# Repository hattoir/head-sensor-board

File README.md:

# 🧠 Serpens Head Sensor Board

> Prototype head sensor PCB for the Serpens snake-shaped pet robot.

Serpensの頭部に搭載するために設計している、
**試作用センサ基板**です。

XIAO ESP32S3 Senseを中心に、

- VL53L1X ToFセンサ ×2
- NSSW157T 白色LED ×2
- MOSFET PWM駆動
- I2C
- Test Points
- 外付けLEDヘッダ

をまとめています。

主な目的は、

- 床端・崖の検出
- 頭部周辺の距離センシング
- LEDによる表現・照明試験

です。

> ⚠️ 現在は設計・製造データ生成まで完了していますが、
> 実基板はまだ発注・製造していません。

---

## 📊 Current Status

| Area | Status |
|---|---|
| Specification | ✅ Complete |
| Schematic | ✅ ERC 0 |
| PCB Layout | ✅ Complete |
| Routing | ✅ Complete |
| DRC | ✅ 0 violations |
| 3D Render | ✅ Complete |
| Gerber / Drill | ✅ Generated |
| BOM | ✅ Generated |
| Manufacturing | ⚪ Not ordered |
| Hardware Verification | ⚪ Not tested |

---

## 🖼 PCB Preview

<!-- ここに今ある3Dレンダリング画像 -->

### Top / Angle View

> ※ 実物写真ではなく、KiCad上の3Dレンダリングです。

---

## ⚙️ Main Components

- XIAO ESP32S3 Sense
- VL53L1X ×2
- NSSW157T ×2
- AO3400A / MOSFET
- I2C pull-up
- Test points

---

## 📐 Board

- Size: **44 × 28 mm**
- Layers: **2**
- M2 mounting holes ×2
- GND plane on both layers
- USB-C access from board edge
- ToF headers on long edges
- LED / external LED headers on right side

---

## 🔬 Verification

現在までに、

- ERC: 0 errors
- DRC: 0 violations
- Unconnected: 0
- Schematic / PCB mismatch: 0
- Silkscreen clearance check
- Gerber verification

を行っています。

ただし、
実機に接続しての電源・ToF・LED動作確認は未実施です。

---

> ## ⚠ 電源の運用上の注意（User 指示 2026-10-01。回路図の注記 H にも同じ内容）
> 1. **5V は試験用の選択肢で、既定は 3V3。** 5V にしたときの合計 **493 mA は USB 2.0 の 500 mA ぎりぎり**（余裕 7 mA）。XIAO の 5V ピンの電流能力は未確認。
> 2. **3V3 は、Wi-Fi 送信・撮影・LED 100 %・ToF ピークを同時にしない運用が必要。** **実機で XIAO の 5V 入力電流を測るまで。**（Seeed の条件不明の 0.65 A を上限と見ると 3V3 の合計は 808 mA = Seeed の「700 mA」の 115 %。[docs/spec.md](docs/spec.md) §4.3）

## 進み具合

| Stage | 内容 | 状態 |
|---|---|---|
| 1 | 仕様と部品表 | 完了（2026-10-01、承認済み） |
| 2 | 回路図と ERC（エラー 0） | 完了（2026-10-01、User 確認済み。ERC 0 件） |
| 3 | 外形と部品配置案（配線なし） | 完了（2026-10-01、User 確認済み） |
| 4 | 外形 44×28 mm、配線、DRC（違反 0・未接続 0・回路図との不一致 0）、3D ビュー、製造データ | **完了（2026-10-02）。製造データ（ガーバー・ドリル・位置ファイル・BOM、ZIP）は [gerbers/](gerbers/) に出した。User の最終確認待ちで、発注はしていない**（[docs/spec.md](docs/spec.md) §6・§7） |

## 配線後の配置（Stage 4）

- **44 × 28 mm、角 R1、M2 穴 ×2**（右の 2 つの角、縁から 2.1 mm）。2 層。`python tools/make_board.py --width W --height H` で、外形・配置・配線・DRC まで作り直せる（[再生成と検証](#再生成と検証)）。
- **USB-C は左の縁**（左下に矢印と「USB-C」の刻印）、**LED（D1/D2）と外付け LED ヘッダ（J3/J4）は右寄りの縁**、**ToF ヘッダ（J1/J2）は上下の長辺の縁**（6 本の信号名を刻印）、TP は上面。**「L」「R」の刻印**あり。
- **下半分 = L チャンネル、上半分 = R チャンネル**（上面から見て USB-C を左にしたとき）。基板上の L/R はロボットの左右とは限らない（ジャンパー線で左右は自由に決められる）。
- 配線: **電源（+3V3・+5V）0.5 mm、LED の電流の経路 0.4 mm、信号 0.25 mm**。GND は両面のベタ。ビア 28 個。I2C の長さは SDA 32 mm・SCL 38 mm。
- **DRC: 違反 0 件**（クリアランス 0.2 mm・縁 0.5 mm・未接続 0・回路図との不一致 0。プロジェクトで「無視」にしていた 4 種の検査も有効にして 0 件）。[docs/drc_report.txt](docs/drc_report.txt)
- **刻印の検査**（`tools/check_board.py`）: 上面の刻印 137 個が、ランド・ほかの刻印と **0.15 mm 以上**、ヘッダの樹脂部（2.54 mm 角）と 0.05 mm 以上、XIAO の外形・基板の縁と離れている。**シルクの線は全部 0.15 mm 以上、文字の高さは 0.8 mm**（2026-10-05 に 0.12 → 0.15 mm に直した。発注先 4 社の公開仕様との照合 → [docs/fab_check.md](docs/fab_check.md)。**JLCPCB の標準の文字（高さ 1.0 mm 以上）だけは未達で、注文画面の「高精度の文字」を選べば通る**。PCBWay・Elecrow・Seeed Fusion は通る）。J1/J2 の信号名は樹脂部の外に 2 段で置き、奥の段には樹脂部の手前までの引き出し線を引いた。
- XIAO の下（ソケットの内側）に小さい部品を置き、裏面は GND ベタ。Sense 拡張ボード（カメラ・microSD）は XIAO の上面に載り、基板側の部品とは干渉しない（出っ張りは未確認。[docs/spec.md](docs/spec.md) §6.5）。

| | |
|---|---|
|  |  |
| 斜め上から（XIAO・拡張ボードは**簡易な箱**。高さは仮） | 真上から（XIAO を外した状態） |

そのほか: [層ごとの配線](docs/routing_layers.png)（表面 F.Cu・裏面 B.Cu）、[3D 真上](docs/board_3d_top.png)、[3D 裏面](docs/board_3d_bottom.png)。

## ToF 小基板のピン配置と、ジャンパー線の対応表（**現物が届いたら埋める**）

J1 / J2 の 6 本は、ToF 小基板（VL53L1X、Amazon B083Z316NC）へジャンパー線でつなぐ。**小基板のピン配置は販売ページに記載がなく、未確認。** ヘッダの並び（上面に信号名を刻印）は仮で、**小基板の並びが違っても基板の作り直しは要らない**（線でつなぎ替える）。J1 = ToF L（下の縁）、J2 = ToF R（上の縁）。pin1 は右端（上面から見て、VIN）。

### J1 / J2 の向き（Stage 3 から 180° 回した理由）と確認結果

- **ピン 1（四角いパッド）は右端**（上面から見て USB-C を左にしたとき）。刻印の並びは**右から** VIN, GND, SCL, SDA, XSHUT, GPIO1（左から読むと GPIO1, XSHUT, SDA, SCL, GND, VIN）。J1 と J2 は同じ向き・同じ x（ピン 1 = 基板の左端から 23.8 mm）。
- Stage 3 ではピン 1 が左端だった。**Stage 4 で 180° 回した理由**: XIAO では SDA（D4）が SCL（D5）の左にある。ヘッダも SDA が SCL の左になる向きにすると、I2C の線が交差せずに、層の乗り換え（ビア）も減る。ヘッダの**信号の割り当て（pin1 = VIN … pin6 = GPIO1）は回路図のまま変えていない**（並べ替えは物理的な向きだけ）。ジャンパー線で小基板につなぐので、向きは線の取り回しにしか影響しない。
- 確認（`python tools/check_board.py`、基板を直接読む）: J1/J2 の 6 パッドすべてで、**基板のネット = 回路図のネット = 刻印の名前**（pin1 +3V3/VIN、pin2 GND、pin3 SCL、pin4 SDA、pin5 XSHUT_L/R、pin6 TOF_L_INT/TOF_R_INT/GPIO1）。四角いパッドは pin1 だけ。

### 小基板の仕様（現物で確認して埋める）

| 項目 | 値 | 確認 |
|---|---|---|
| 基板上の印字（ピンの名前、端から順に） | （現物で確認） | 🔴 未確認 |
| ピンの数・ピッチ・オス/メス | （現物で確認） | 🔴 未確認 |
| 電源電圧 | 3.3〜5 V（商品ページの記載） | 🟡 |
| 基板上のプルアップ（SDA / SCL / XSHUT）、レギュレータ、レベルシフタの有無 | （現物で確認） | 🔴 未確認 |
| I2C アドレス | ST のデータシートの既定は 0x29（7 bit）。**小基板で変わるかは未確認** | 🟡 |

### 対応表（J1 / J2 のピン ↔ 小基板のピン）

| J1 / J2 のピン | 基板の信号名 | つなぎ先 | 小基板のピン（印字）→ **現物で記入** | ジャンパー線 | メモ |
|---|---|---|---|---|---|
| 1 | VIN | XIAO の 3V3 | （　　　　） | （　　　　） | 小基板が 3.3〜5 V 対応なので 3V3 を使う。**VIN と GND を逆につながない**（小基板の保護は未確認） |
| 2 | GND | GND | （　　　　） | （　　　　） | |
| 3 | SCL | I2C SCL（D5） | （　　　　） | （　　　　） | プルアップは基板側 R14（3.3 kΩ、既定は未実装）か小基板側 |
| 4 | SDA | I2C SDA（D4） | （　　　　） | （　　　　） | 同 R13（既定は未実装） |
| 5 | XSHUT | J1: XSHUT_L（D0）／J2: XSHUT_R（D1） | （　　　　） | （　　　　） | 10 kΩ で 3V3 にプルアップ済み |
| 6 | GPIO1 | J1: R15 経由で D8／J2: R16 経由で D9 | （　　　　） | （　　　　） | R15/R16（0 Ω）は**既定で未実装**（つながない）。割り込みを使うときだけ実装 |

**2 個の小基板は I2C アドレスが同じ**なので、XSHUT で 1 個ずつ起動して、片方のアドレスを変える（[docs/spec.md](docs/spec.md) §3）。

## フォルダ構成

| 場所 | 中身 |
|---|---|
| （直下） | KiCad プロジェクト（`.kicad_pro` / `.kicad_sch` / `.kicad_pcb`、`sym-lib-table` / `fp-lib-table`） |
| `.ai/` | 閉ループの記録（`CURRENT_HANDOFF.md`、`PROJECT_STATE.json`、`TASK_GRAPH.json`、`DECISIONS.jsonl`、`EXPERIMENTS.jsonl`、`EVIDENCE.jsonl`。追記専用の `.jsonl`）。次のセッションはここから再開する |
| `docs/` | [spec.md](docs/spec.md)（仕様・計算・配置・配線・検証）、[fab_check.md](docs/fab_check.md)（発注先の公開仕様との照合）、[bringup_plan.md](docs/bringup_plan.md)（届いてからの確認手順 = Human Gate）・[bringup_nets.md](docs/bringup_nets.md)（導通の確認表）、[bom.md](docs/bom.md)・`bom.csv`（部品表。**Stage 2 のまま**。BOM の出力時に再生成）、`erc_report*.txt`・`drc_report.txt`、回路図 PDF、配線後の配置図・層ごとの配線・3D ビュー（PNG）、`routes.json`（配線の結果）、`led_budget_output.txt` |
| `libs/` | 自作のシンボル・フットプリント（**KiCad 標準ライブラリに無いものだけ**。下の「ライブラリの出典」） |
| `3dmodels/` | 3D ビュー用の**簡易モデル**（`.wrl`。XIAO + Sense 拡張ボード、LED の箱）。`tools/gen_3d.py` で生成。見た目の確認用 |
| `gerbers/` | **製造データ**（ガーバー、ドリル、位置ファイル、BOM、`head-sensor-board_gerbers.zip`、README）。2026-10-02 に出した。**発注はしていない**（User の最終確認のあと）。中身の説明は [gerbers/README.md](gerbers/README.md) |
| `tools/` | 計算・生成・検証のスクリプト（下の「再生成と検証」） |

## 数値・部品名の出典

確認状態: ✅ 原本（データシート・公式図面）で確認 ／ 🟡 販売ページ・Wiki で確認 ／ 🔴 未確認・仮定。**確認できていないものは、`docs/spec.md` の各表に「未確認」と書いてある。**

| 対象 | 出典 | 確認 |
|---|---|---|
| NSSW157T（Nichia）: 外形 3.0×1.4×0.52、VF、IF max、推奨ランド | [Nichia STS-DA1-1913（秋月配布 PDF）](https://akizukidenshi.com/goodsaffix/nssw157t.pdf)、[秋月 116884](https://akizukidenshi.com/catalog/g/g116884/) | ✅ |
| AO3400A（Alpha & Omega）: VGS(th)、RDS(on) @2.5 V、SOT-23 | [AOS データシート Rev 3.1](https://www.aosmd.com/res/data_sheets/AO3400A.pdf) | ✅ |
| Si2302CDS（Vishay）: VGS(th)、RDS(on) @2.5 V、1=G 2=S 3=D | [Vishay 68645（S12-2336 Rev D）](https://www.vishay.com/docs/68645/si2302cds.pdf) | ✅ |
| VL53L1X（ST）: AVDD 2.6〜3.5 V、消費電流、XSHUT・I2C・既定アドレス、最短 4 cm | ST DS12385 Rev 8（[複製 PDF](https://www.makerguides.com/wp-content/uploads/2024/10/VL53L1X-Datasheet.pdf)。ST 公式サイトの版では未照合） | ✅（複製） |
| ESP32-S3: Wi-Fi 送信ピーク 340 mA、GPIO の IOH/IOL、VOH、GPIO3 ストラッピング | [Espressif ESP32-S3 Datasheet v2.2](https://www.espressif.com/sites/default/files/documentation/esp32-s3_datasheet_en.pdf)（表 5-7・表 5-4・§3.4） | ✅ |
| XIAO ESP32S3: ピン配置、GPIO 番号、3V3 出力 700 mA、Webcam の消費電流、Sense が使う GPIO | [Seeed wiki](https://wiki.seeedstudio.com/xiao_esp32s3_getting_started/)（PDF のデータシートは見つからず） | 🟡 |
| XIAO の穴パターン（ピッチ 2.54、行間隔 15.25、穴 φ1.02、外形 21×17.8） | [Seeed "XIAO Series Package and PCB Design" p.7](https://www.seeedstudio.com/blog/wp-content/uploads/2022/08/Seeed-Studio-XIAO-Series-Package-and-PCB-Design.pdf)（シリーズ共通図。S3 個別ではない） | ✅（共通図） |
| VL53L1X 小基板（Amazon B083Z316NC）: 12×17×3.2 mm、3.3〜5 V | [商品ページ](https://www.amazon.co.jp/dp/B083Z316NC)。**ピン配置・プルアップ・アドレスの記載なし** | 🔴 |
| 頭の外形 幅 100 / 高さ 74 / 長さ 78 mm、ToF・LED の位置 | `serpens/ai-shared/design-state.md`、`serpens/docs/design/tof_board_placement_2026-09-30.md`（Design の概念値 = CAD_CONCEPT / ASSUMED） | 🔴（概念値） |
| T6 / T4 の試験の内容 | `serpens/ai-shared/HARDWARE_TODO.md` HT-005 / HT-011、HG-H2 の `hardware_test_plan.md`・`tof_cliff.md`（Engineering の worktree `agent/engineering-h1-j1`、未マージ） | 🟡 |

## ライブラリの出典

`libs/` にあるのは、KiCad 標準ライブラリに無い（または標準を少し変えた）7 点だけ（`python tools/gen_libs.py` で生成）。

| 名前 | 種類 | 理由 | 出典 |
|---|---|---|---|
| `XIAO_ESP32S3` | シンボル（14 ピン。電源ピンを上下に置いた表示。ピン番号は実物のまま） | 標準ライブラリに XIAO ESP32S3 が無い | ピン配置は Seeed wiki |
| `ToF_Header_1x06` | シンボル（ピン名つき。**並びは仮 = 未確認**） | ピン名（VIN, GND, SCL, SDA, XSHUT, GPIO1）を回路図に出すため | 自作 |
| `Q_NMOS_GSD` | シンボル（SOT-23 の 1=G 2=S 3=D） | 標準の `Device:Q_NMOS` はピン番号が D/G/S の文字で、SOT-23 のパッド番号と合わない | 図形は KiCad 標準 `Device:Q_NMOS` を流用、ピン番号だけ数字に |
| `XIAO_ESP32S3_THT_2x7_P2.54mm` | フットプリント（穴パターン） | 標準には表面実装用の `RF_Module:MCU_Seeed_ESP32C3` しか無く、2.54 mm の穴パターンが無い | Seeed 公式図面 p.7（行間隔 15.24 mm = 図面の 15.25 を 0.6 in に丸めた、穴 φ1.02、パッド φ1.8）。**コートヤードはピン列の帯だけ**（XIAO の下に小さい部品を置くため。Stage 3） |
| `TestPoint_Pad_D1.5mm_NoSilk` | フットプリント（TP） | 標準の `TestPoint:TestPoint_Pad_D1.5mm` の銀色の輪（半径 0.95 mm）が、近くに置く名前の刻印と重なるため | KiCad 標準 `TestPoint_Pad_D1.5mm` から輪だけ除いた（パッド φ1.5、コートヤード 半径 1.05）。Stage 3 |
| `PinHeader_1x06_P2.54mm_NoSilk` | フットプリント（J1/J2。ToF ヘッダ） | 標準の `Connector_PinHeader_2.54mm:PinHeader_1x06_P2.54mm_Vertical` の上面シルクの外枠が、6 本の信号名の刻印と重なるため | KiCad 標準から**上面シルクの外枠（線・四角）だけ除いた**（ランド・穴・コートヤード・Fab・3D は標準のまま）。Stage 4 |
| `LED_Nichia_NSSW157T` | フットプリント（T 字のランド） | 標準ライブラリに同寸法のものが無い | Nichia STS-DA1-1913 p.4–5（全長 4.0、カソード 0.6+1.66、ギャップ 0.5、アノード 0.64+0.6、高さ 1.55/0.86） |

3D モデル: 標準ライブラリにある部品（ピンヘッダ、抵抗、MOSFET など）は標準のモデル。**XIAO + Sense 拡張ボードと NSSW157T は `3dmodels/` の簡易な箱**（高さは仮。見た目の確認用で、寸法の根拠にしない）。

## 再生成と検証

```bash
python tools/led_budget.py        # LED 電流・3V3/5V の総電流の計算（docs/led_budget_output.txt）
python tools/gen_libs.py          # 自作ライブラリ（libs/）と sym-lib-table / fp-lib-table
python tools/gen_3d.py            # 簡易 3D モデル（3dmodels/）
python tools/gen_schematic.py     # 回路図（※KiCad で手直しした後は実行しない。手直しが消える）
python tools/check_netlist.py     # ネットリストを期待と照合、回路図のピン番号がフットプリントのパッドに存在するか
python tools/make_board.py [--width 44 --height 28] [--reuse-routes]
                                  # 外形・配置（gen_pcb.py）→ 自動配線（route.py、numpy + scipy）→ トラック・ビア・GND ベタ（apply_routes.py）→ DRC。
                                  # ※既存の基板を作り直す（KiCad で手で直した配線は消える）。約 30 秒
                                  # --reuse-routes: ランドの位置を変えず刻印だけ直したとき、配線をやり直さない（DRC で整合を確かめる）。自動配線は約 1〜10 分（CPU が空いていれば 1 分以内）
"C:/Program Files/KiCad/10.0/bin/python.exe" tools/check_board.py   # J1/J2 のネット・パッド・刻印の照合、刻印のすきまの検査（問題があれば終了コード 1）
"C:/Program Files/KiCad/10.0/bin/python.exe" tools/render_routed.py   # 配線後の配置図・層ごとの配線（docs/*.png）
python tools/render_3d.py         # KiCad の 3D ビュー（docs/board_3d_*.png）
python tools/make_outputs.py [--bom]   # ERC・DRC・回路図 PDF・BoardRepo 用 zip（--bom で BOM も）
python tools/make_fabrication.py  # gerbers/（ガーバー・ドリル・位置ファイル・BOM・ZIP）。**User の確認のあとにだけ**
python tools/verify_gerbers.py    # 出力した ZIP を別のライブラリ（gerbonara）で読み直して、基板と照合（pip install gerbonara）
python tools/compare_gerbers.py --current   # gerbers/ が今の基板から作り直した図形と同じか（古くなっていないか）。2 つの ZIP / git の ref の比較にも使える
"C:/Program Files/KiCad/10.0/bin/python.exe" tools/check_fab_rules.py [--md docs/fab_check.md]   # 発注先 4 社の公開仕様（tools/fab_rules.json）との照合
python tools/gen_bringup_tables.py   # 導通の確認表 docs/bringup_nets.md（回路図から）
python tools/run_all_checks.py    # 上の検査を全部まとめて回す（何も書き換えない。発注の前に）
```
KiCad は `C:/Program Files/KiCad/10.0/bin/kicad-cli.exe`（PATH には入っていない）。`tools/pcb_template.kicad_pcb` は空の基板（層・設定だけ。`gen_pcb.py` が毎回ここから作る）。
自動配線は KiCad の Python に scipy が無いため、基板の形状を `docs/placement_geometry.json` に書き出し → システムの Python で配線 → `docs/routes.json` → KiCad の Python で基板に書き戻す、の 3 段。

## BoardRepo について

- BoardRepo は「アップロードのたびに番号つきの版ができる」方式で、閲覧・MCP は OAuth のサインインが要る（[boardrepo.com](https://boardrepo.com)）。**Agent 側からは取り込みを確認できない。User が手動でアップロードする。**
- `snake-main-board` の GitHub リポジトリにも、BoardRepo の Webhook・チェック・コミットステータスは残っていない（確認済み）。
- **アップロード用の束**: `C:\2026\Serpens_Home AI\head-sensor-board_upload.zip`（`tools/make_outputs.py` が作る。Git には入れない）。中身: `.gitignore`、`README.md`、`.kicad_pro`、`.kicad_sch`、`.kicad_pcb`（**Stage 4: 44×28 mm、配線済み・GND ベタ。ガーバーではない**）、`sym-lib-table`、`fp-lib-table`、`libs/`（自作ライブラリ）、`3dmodels/`（簡易 3D モデル）。別フォルダに展開して、ERC 0 件・DRC 0 件になることを確認する（make_outputs 後に実施）。
- **アップロードして表示できたかは User の確認が要る。**

## 注意

- `*-backups/`、`fp-info-cache`、`*.kicad_prl`、ロックファイル、自動保存、`*_upload.zip` は Git に入れない（`.gitignore`）。
- このフォルダは、親の `serpens`（ロボット制御のリポジトリ）とは**別の Git リポジトリ**（入れ子）。親側は `.git/info/exclude` で無視している。`snake-main-board` とも別。

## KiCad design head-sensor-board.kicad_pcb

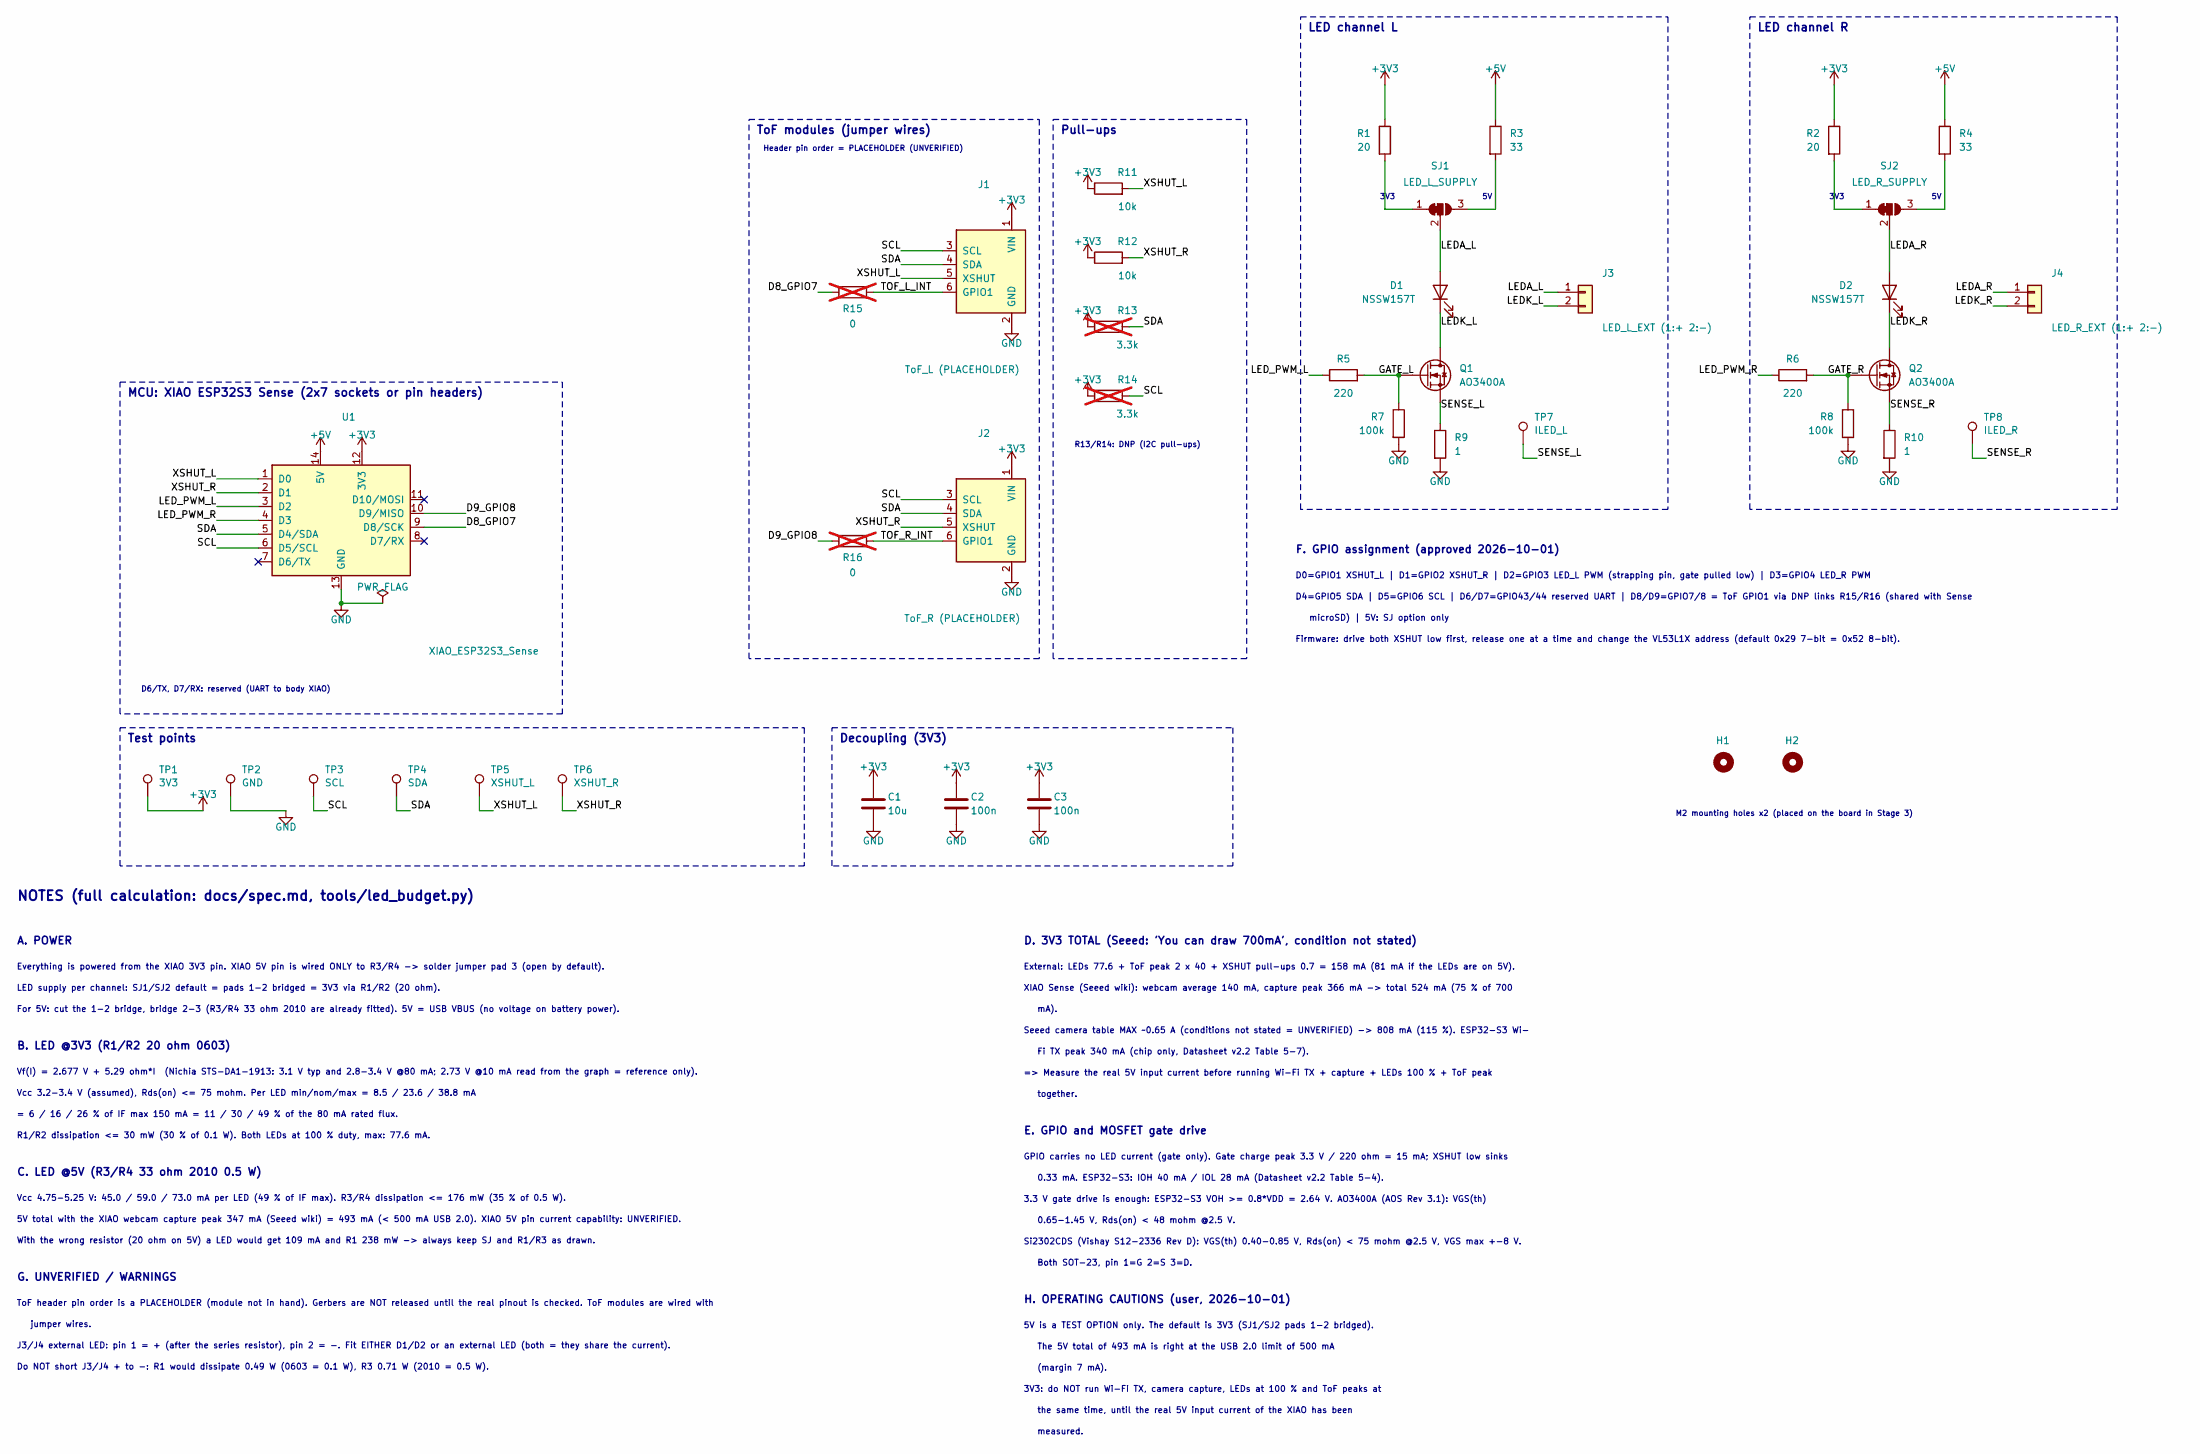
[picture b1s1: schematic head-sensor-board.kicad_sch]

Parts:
C1: 10u; C_0805_2012Metric; Rating 10 V X5R 0805; MPN ceramic capacitor 10uF
C2, C3: 100n; C_0603_1608Metric; Rating 16 V X7R 0603; MPN ceramic capacitor 100nF
D1, D2: NSSW157T; LED_Nichia_NSSW157T; Rating IF 150 mA max; VF 2.8-3.4 V @80 mA; 3.0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; MPN NSSW157T
H1, H2: MountingHole_2.2mm_M2; MPN M2 mounting hole (no part)
J1: ToF_L (PLACEHOLDER); PinHeader_1x06_P2.54mm_NoSilk; Rating 2.54 mm pitch; MPN PinHeader 1x06 2.54 mm
J2: ToF_R (PLACEHOLDER); PinHeader_1x06_P2.54mm_NoSilk; Rating 2.54 mm pitch; MPN PinHeader 1x06 2.54 mm
J3: LED_L_EXT (1:+ 2:-); PinHeader_1x02_P2.54mm_Vertical; Rating current-limited node (after R1/R3); MPN PinHeader 1x02 2.54 mm
J4: LED_R_EXT (1:+ 2:-); PinHeader_1x02_P2.54mm_Vertical; Rating current-limited node (after R1/R3); MPN PinHeader 1x02 2.54 mm
Q1, Q2: AO3400A; SOT-23; Rating 30 V 5.7 A VGS(th) 0.65-1.45 V RDS(on)<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; MPN AO3400A (alt. Si2302CDS)
R1, R2: 20; R_0603_1608Metric; Rating 0.1 W (0603); MPN chip resistor 20 ohm
R3, R4: 33; R_2010_5025Metric; Rating 0.5 W (2010); MPN chip resistor 33 ohm
R5, R6: 220; R_0603_1608Metric; Rating 0.1 W (0603); MPN chip resistor 220 ohm
R7, R8: 100k; R_0603_1608Metric; Rating 0.1 W (0603); MPN chip resistor 100k ohm
R9, R10: 1; R_0603_1608Metric; Rating 0.1 W (0603) 1 %; MPN chip resistor 1 ohm
R11, R12: 10k; R_0603_1608Metric; Rating 0.1 W (0603); MPN chip resistor 10k ohm
R13, R14: 3.3k; R_0603_1608Metric; Rating 0.1 W (0603); MPN chip resistor 3.3k ohm; not fitted
R15, R16: 0; R_0603_1608Metric; Rating 0 ohm jumper; MPN chip resistor 0 ohm; not fitted
SJ1: LED_L_SUPPLY; SolderJumper-3_P1.3mm_Bridged12_RoundedPad1.0x1.5mm; MPN solder jumper (PCB pads)
SJ2: LED_R_SUPPLY; SolderJumper-3_P1.3mm_Bridged12_RoundedPad1.0x1.5mm; MPN solder jumper (PCB pads)
TP1: 3V3; TestPoint_Pad_D1.5mm_NoSilk; MPN test point pad
TP2: GND; TestPoint_Pad_D1.5mm_NoSilk; MPN test point pad
TP3: SCL; TestPoint_Pad_D1.5mm_NoSilk; MPN test point pad
TP4: SDA; TestPoint_Pad_D1.5mm_NoSilk; MPN test point pad
TP5: XSHUT_L; TestPoint_Pad_D1.5mm_NoSilk; MPN test point pad
TP6: XSHUT_R; TestPoint_Pad_D1.5mm_NoSilk; MPN test point pad
TP7: ILED_L; TestPoint_Pad_D1.5mm_NoSilk; MPN test point pad
TP8: ILED_R; TestPoint_Pad_D1.5mm_NoSilk; MPN test point pad
U1: XIAO_ESP32S3_Sense; XIAO_ESP32S3_THT_2x7_P2.54mm; Rating 3V3 out 700 mA (Seeed wiki, condition n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; MPN Seeed XIAO ESP32S3 Sense

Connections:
+3V3: C1.1, C2.1, C3.1, J1.1 (VIN), J2.1 (VIN), R1.1, R2.1, R11.1, R12.1, R13.1, R14.1, TP1.1, U1.12 (3V3)
+5V: R3.1, R4.1, U1.14 (5V)
/D8_GPIO7: R15.1, U1.9 (D8/SCK)
/D9_GPIO8: R16.1, U1.10 (D9/MISO)
/GATE_L: Q1.1 (G), R5.2, R7.1
/GATE_R: Q2.1 (G), R6.2, R8.1
/LEDA_L: D1.2 (A), J3.1, SJ1.2 (C)
/LEDA_R: D2.2 (A), J4.1, SJ2.2 (C)
/LEDK_L: D1.1 (K), J3.2, Q1.3 (D)
/LEDK_R: D2.1 (K), J4.2, Q2.3 (D)
/LED_PWM_L: R5.1, U1.3 (D2)
/LED_PWM_R: R6.1, U1.4 (D3)
/SCL: J1.3 (SCL), J2.3 (SCL), R14.2, TP3.1, U1.6 (D5/SCL)
/SDA: J1.4 (SDA), J2.4 (SDA), R13.2, TP4.1, U1.5 (D4/SDA)
/SENSE_L: Q1.2 (S), R9.1, TP7.1
/SENSE_R: Q2.2 (S), R10.1, TP8.1
/TOF_L_INT: J1.6 (GPIO1), R15.2
/TOF_R_INT: J2.6 (GPIO1), R16.2
/XSHUT_L: J1.5 (XSHUT), R11.2, TP5.1, U1.1 (D0)
/XSHUT_R: J2.5 (XSHUT), R12.2, TP6.1, U1.2 (D1)
GND: C1.2, C2.2, C3.2, J1.2 (GND), J2.2 (GND), R7.2, R8.2, R9.2, R10.2, TP2.1, U1.13 (GND)
unnamed: R1.2, SJ1.1 (A)
unnamed: R3.2, SJ1.3 (B)
unnamed: R2.2, SJ2.1 (A)
unnamed: R4.2, SJ2.3 (B)

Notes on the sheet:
MCU: XIAO ESP32S3 Sense (2x7 sockets or pin headers)
D6/TX, D7/RX: reserved (UART to body XIAO)
ToF modules (jumper wires)
Header pin order = PLACEHOLDER (UNVERIFIED)
Pull-ups
R13/R14: DNP (I2C pull-ups)
LED channel L
3V3
LED channel R
Test points
Decoupling (3V3)
M2 mounting holes x2 (placed on the board in Stage 3)
NOTES (full calculation: docs/spec.md, tools/led_budget.py)
A. POWER
Everything is powered from the XIAO 3V3 pin. XIAO 5V pin is wired ONLY to R3/R4 -> solder jumper pad 3 (open by default).
LED supply per channel: SJ1/SJ2 default = pads 1-2 bridged = 3V3 via R1/R2 (20 ohm).
For 5V: cut the 1-2 bridge, bridge 2-3 (R3/R4 33 ohm 2010 are already fitted). 5V = USB VBUS (no voltage on battery power).
B. LED @3V3 (R1/R2 20 ohm 0603)
Vf(I) = 2.677 V + 5.29 ohm*I (Nichia STS-DA1-1913: 3.1 V typ and 2.8-3.4 V @80 mA; 2.73 V @10 mA read from the graph = reference only).
Vcc 3.2-3.4 V (assumed), Rds(on) <= 75 mohm. Per LED min/nom/max = 8.5 / 23.6 / 38.8 mA
= 6 / 16 / 26 % of IF max 150 mA = 11 / 30 / 49 % of the 80 mA rated flux.
R1/R2 dissipation <= 30 mW (30 % of 0.1 W). Both LEDs at 100 % duty, max: 77.6 mA.
C. LED @5V (R3/R4 33 ohm 2010 0.5 W)
Vcc 4.75-5.25 V: 45.0 / 59.0 / 73.0 mA per LED (49 % of IF max). R3/R4 dissipation <= 176 mW (35 % of 0.5 W).
5V total with the XIAO webcam capture peak 347 mA (Seeed wiki) = 493 mA (< 500 mA USB 2.0). XIAO 5V pin current capability: UNVERIFIED.
With the wrong resistor (20 ohm on 5V) a LED would get 109 mA and R1 238 mW -> always keep SJ and R1/R3 as drawn.
G. UNVERIFIED / WARNINGS
ToF header pin order is a PLACEHOLDER (module not in hand). Gerbers are NOT released until the real pinout is checked. ToF modules are wired with
jumper wires.
J3/J4 external LED: pin 1 = + (after the series resistor), pin 2 = -. Fit EITHER D1/D2 or an external LED (both = they share the current).
Do NOT short J3/J4 + to -: R1 would dissipate 0.49 W (0603 = 0.1 W), R3 0.71 W (2010 = 0.5 W).
D. 3V3 TOTAL (Seeed: 'You can draw 700mA', condition not stated)
External: LEDs 77.6 + ToF peak 2 x 40 + XSHUT pull-ups 0.7 = 158 mA (81 mA if the LEDs are on 5V).
XIAO Sense (Seeed wiki): webcam average 140 mA, capture peak 366 mA -> total 524 mA (75 % of 700
mA).
Seeed camera table MAX ~0.65 A (conditions not stated = UNVERIFIED) -> 808 mA (115 %). ESP32-S3 Wi-
Fi TX peak 340 mA (chip only, Datasheet v2.2 Table 5-7).
=> Measure the real 5V input current before running Wi-Fi TX + capture + LEDs 100 % + ToF peak
together.
E. GPIO and MOSFET gate drive

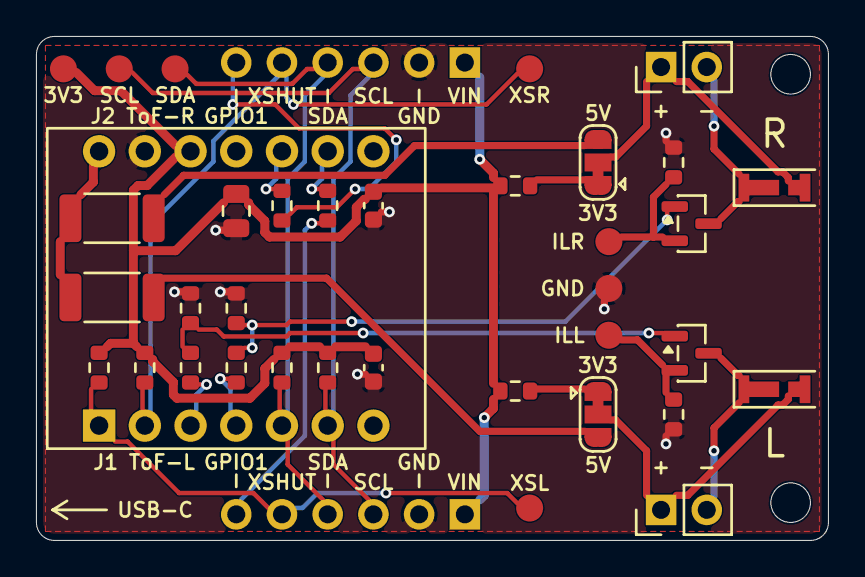
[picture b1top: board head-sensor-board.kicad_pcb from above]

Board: 2 copper layers, 44.0 x 28.0 mm, 40 parts (0 on the bottom side), 25 nets.

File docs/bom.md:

# BOM（部品表）— head-sensor-board Rev A（製造データ出力時）

**回路図から `tools/make_outputs.py` が作る。手で直さない**（直すときは回路図 → 再生成）。生の書き出しは [bom.csv](bom.csv)。
DNP = 既定で実装しない（フットプリントだけ置く）。**購入先・品番・価格の列は、User が秋月などで調べて埋める**（ここでは仕様だけ）。
抵抗・コンデンサは汎用品（型番の指定なし）。**仕様（値・パッケージ・定格）を満たせばよい。** 許容差: R9/R10（電流検出 1 Ω）は ±1 %、ほかの抵抗は ±5 % 以内、R15/R16 は 0 Ω ジャンパー。コンデンサは C1 が X5R 以上・10 V 以上、C2/C3 が X7R・16 V 以上。

## 1. 基板に載せる部品（回路図から）

| 記号 | 数量 | 値 | パッケージ（フットプリント） | 型番・種類 | 定格 | DNP | 備考 | 購入先・品番・価格 |
|---|---|---|---|---|---|---|---|---|
| U1 | 1 | XIAO_ESP32S3_Sense | `head-sensor-board:XIAO_ESP32S3_THT_2x7_P2.54mm` | Seeed XIAO ESP32S3 Sense | 3V3 out 700 mA (Seeed wiki, condition not stated) |  | Akizuki 118079. Mount on 2x 1x7 sockets (or pin headers). USB-C side = up in the drawing | （User が調査） |
| J1, J2 | 2 | ToF_L (PLACEHOLDER) / ToF_R (PLACEHOLDER) | `head-sensor-board:PinHeader_1x06_P2.54mm_NoSilk` | PinHeader 1x06 2.54 mm | 2.54 mm pitch |  | VL53L1X small module (Amazon B083Z316NC) on jumper wires. PIN ORDER IS A PLACEHOLDER - UNVERIFIED (module not in hand) | （User が調査） |
| J3, J4 | 2 | LED_L_EXT (1:+ 2:-) / LED_R_EXT (1:+ 2:-) | `Connector_PinHeader_2.54mm:PinHeader_1x02_P2.54mm_Vertical` | PinHeader 1x02 2.54 mm | current-limited node (after R1/R3) |  | External LED: pin 1 = + (LEDA, after the series resistor), pin 2 = - (LEDK). Do NOT short + to - | （User が調査） |
| SJ1, SJ2 | 2 | LED_L_SUPPLY / LED_R_SUPPLY | `Jumper:SolderJumper-3_P1.3mm_Bridged12_RoundedPad1.0x1.5mm` | solder jumper (PCB pads) | - |  | Default: pads 1-2 bridged = 3V3 via R1/R2. For 5V: cut the 1-2 bridge, bridge 2-3 (via R3/R4) | （User が調査） |
| D1,D2 | 2 | NSSW157T | `head-sensor-board:LED_Nichia_NSSW157T` | NSSW157T（Nichia） | IF 150 mA max; VF 2.8-3.4 V @80 mA; 3.0x1.4x0.52 mm |  | Akizuki 116884. White chip LED, height 0.52 mm | （User が調査） |
| Q1,Q2 | 2 | AO3400A | `Package_TO_SOT_SMD:SOT-23` | AO3400A (alt. Si2302CDS)（Alpha & Omega (alt. Vishay)） | 30 V 5.7 A VGS(th) 0.65-1.45 V RDS(on)<48 mohm @2.5 V (alt. Si2302CDS 20 V 2.6 A 0.40-0.85 V <75 mohm) |  | SOT-23 pin 1=G 2=S 3=D. Gate driven by 3.3 V logic | （User が調査） |
| R1,R2 | 2 | 20 | `Resistor_SMD:R_0603_1608Metric` | chip resistor 20 ohm | 0.1 W (0603) |  | LED current limit @3V3 (20 ohm: 8.5/23.6/38.8 mA min/nom/max) | （User が調査） |
| R3,R4 | 2 | 33 | `Resistor_SMD:R_2010_5025Metric` | chip resistor 33 ohm | 0.5 W (2010) |  | LED current limit @5V (33 ohm 2010: 45/59/73 mA min/nom/max). Fitted, used only when SJ is set to 5V | （User が調査） |
| R5,R6 | 2 | 220 | `Resistor_SMD:R_0603_1608Metric` | chip resistor 220 ohm | 0.1 W (0603) |  | Gate series resistor (limits the gate charge peak to 15 mA) | （User が調査） |
| R7,R8 | 2 | 100k | `Resistor_SMD:R_0603_1608Metric` | chip resistor 100k ohm | 0.1 W (0603) |  | Gate pull-down: LED off during reset/boot (GPIO3 is a strapping pin) | （User が調査） |
| R9,R10 | 2 | 1 | `Resistor_SMD:R_0603_1608Metric` | chip resistor 1 ohm | 0.1 W (0603) 1 % |  | Current sense: TP ILED voltage = 1 mV per mA (1 %) | （User が調査） |
| R11, R12 | 2 | 10k | `Resistor_SMD:R_0603_1608Metric` | chip resistor 10k ohm | 0.1 W (0603) |  | XSHUT pull-up (ST DS12385 2.4: XSHUT must always be driven; 10k recommended) / XSHUT pull-up (ST DS12385 2.4) | （User が調査） |
| R13, R14 | 2 | 3.3k | `Resistor_SMD:R_0603_1608Metric` | chip resistor 3.3k ohm | 0.1 W (0603) | **DNP** | I2C pull-up. DNP: fit only if the module has none (ST Table 4: 3.6k for CL<=90 pF) / I2C pull-up. DNP: fit only if the module has none | （User が調査） |
| R15,R16 | 2 | 0 | `Resistor_SMD:R_0603_1608Metric` | chip resistor 0 ohm | 0 ohm jumper | **DNP** | GPIO1 link to XIAO D8/D9 (shares the Sense microSD SPI pins). Default: not fitted | （User が調査） |
| C1 | 1 | 10u | `Capacitor_SMD:C_0805_2012Metric` | ceramic capacitor 10uF | 10 V X5R 0805 |  | 3V3 bulk: LED PWM + ToF peaks (2 x 40 mA) | （User が調査） |
| C2, C3 | 2 | 100n | `Capacitor_SMD:C_0603_1608Metric` | ceramic capacitor 100nF | 16 V X7R 0603 |  | Bypass near ToF header J1 / Bypass near ToF header J2 | （User が調査） |

回路図に出るが部品ではないもの: **TP1〜TP8**（テストポイントのパッド φ1.5 mm、自作 `TestPoint_Pad_D1.5mm_NoSilk`。部品なし）、**H1, H2**（M2 取付穴 φ2.2、`MountingHole:MountingHole_2.2mm_M2`）、**SJ1, SJ2**（半田ジャンパーのパッド。部品なし）。

## 2. 基板の外の部品（組み立てに必要）

| 用途 | 数量 | 品名 | パッケージ・寸法 | 定格・メモ | DNP | 備考 |
|---|---|---|---|---|---|---|
| U1 用 | 2 | ピンソケット 1×7（メス） | 2.54 mm ピッチ、スルーホール | 高さ 8.5 mm と仮定（購入品で確認） | — | XIAO を載せる。ピンヘッダ（オス）に替えてもよい（同じパッド） |
| XIAO 側 | 2 | ピンヘッダ 1×7（オス） | 2.54 mm ピッチ | Seeed の 7 pin ヘッダ SKU 320020159 は全長 10.34 / 上 6.00 / 下 1.80 mm | — | XIAO に同梱かは**未確認**。無ければ購入 |
| J1, J2 用 | 12 | ジャンパー線（ToF 小基板との接続） | ToF 小基板のピンの種類による（メス–メス / メス–オス） | — | — | ToF のピン配置・コネクタは**未確認**。候補: 秋月 100288「ブレッドボード・ジャンパーワイヤ 14 種類×10 本」（`秋月_購入リスト_20260930.md` に記載。**xlsx の購入リストには無い**） |
| H1, H2 用 | 2 | M2 ねじ（+ スペーサ） | M2、取付穴 φ2.2 | — | — | 頭への取り付け方法が未定のため**未決**（任意） |

## 3. 仕様の根拠（主なもの）

- **NSSW157T**: Nichia STS-DA1-1913（秋月配布）— IF max 150 mA、VF 2.8〜3.4 V @80 mA、3.0×1.4×0.52 mm。
- **AO3400A**: Alpha & Omega Rev 3.1（2023-07）— 30 V / 5.7 A、VGS(th) 0.65〜1.45 V、RDS(on) < 48 mΩ @VGS=2.5 V、VGS 最大 ±12 V、SOT-23。**Si2302CDS**（Vishay S12-2336 Rev D）— 20 V / 2.6 A、VGS(th) 0.40〜0.85 V、RDS(on) < 75 mΩ @2.5 V、VGS 最大 ±8 V、SOT-23（1=G, 2=S, 3=D）。どちらも 3.3 V ロジックで駆動できる（ESP32-S3 の VOH 最小 2.64 V でも VGS(th) 最大の 1.8 倍以上）。
- **R3/R4（5V 用 33 Ω 2010）**: 最悪時 176 mW = 0.5 W の 35 %（`tools/led_budget.py`）。0603/0805 では足りない（1206 でも 70 % で 50 % 基準を超える）。
- **R1/R2（3V3 用 20 Ω 0603）**: 最悪時 30 mW = 0.1 W の 30 %。
- **C1（10 µF）**: 3V3 電源だめ。X5R の 10 µF は DC バイアスで容量が下がるので、10 V 以上を選ぶ。

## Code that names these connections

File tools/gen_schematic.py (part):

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    s.no_connect(s.pin("U1", 7))
    s.text("D6/TX, D7/RX: reserved (UART to body XIAO)", (g(36), g(113)), 1.0)
    s.no_connect(s.pin("U1", 11))                                   # D10 unused
    s.stub("U1", 10, "D9_GPIO8", 7.62)
    s.stub("U1", 9, "D8_GPIO7", 7.62)
    s.no_connect(s.pin("U1", 8))                                     # D7/RX reserved
    s.power("+5V", s.pin("U1", 14))
    s.power("+3V3", s.pin("U1", 12))
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    s.text("Header pin order = PLACEHOLDER (UNVERIFIED)", (g(126), g(34) + 1.0), 1.0)
    tof_fields = {"MPN": "PinHeader 1x06 2.54 mm", "Rating": "2.54 mm pitch",
                  "Notes": "VL53L1X small module (Amazon B083Z316NC) on jumper wires. PIN ORDER IS A PLACEHOLDER - UNVERIFIED (module not in hand)"}
    for ref, val, at, sh, inte, dnet in (("J1", "ToF_L (PLACEHOLDER)", (g(158), g(52)), "XSHUT_L", "TOF_L_INT", "D8_GPIO7"),
                                          ("J2", "ToF_R (PLACEHOLDER)", (g(158), g(88)), "XSHUT_R", "TOF_R_INT", "D9_GPIO8")):
        s.place("head-sensor-board:ToF_Header_1x06", ref, val, at, 0, "head-sensor-board:PinHeader_1x06_P2.54mm_NoSilk",
                fields=tof_fields, ref_off=(0, -16.0, "center"), val_off=(-4.0, 18.0, "center"))
        s.power("+3V3", s.pin(ref, 1))
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        s.stub(ref, 3, "SCL", 7.62)
        s.stub(ref, 4, "SDA", 7.62)
        s.stub(ref, 5, sh, 7.62)
        # GPIO1 -> 0 ohm link (DNP) -> XIAO D8 / D9
        p6 = s.pin(ref, 6)
        lref = "R15" if ref == "J1" else "R16"
        lx = round(p6[0] - 12.7 - 3.81, 4)
        res(lref, "0", (lx, p6[1]), 90, R0603, "GPIO1 link to XIAO D8/D9 (shares the Sense microSD SPI pins). Default: not fitted",
            "0 ohm jumper", dnp=True, ref_off=(0, 3.0, "center"), val_off=(0, 5.8, "center"))
        s.wire(p6, s.pin(lref, 2))
        s.stub(lref, 1, dnet, 2.54)
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            "Si2302CDS (Vishay S12-2336 Rev D): VGS(th) 0.40-0.85 V, Rds(on) < 75 mohm @2.5 V, VGS max +-8 V. Both SOT-23, pin 1=G 2=S 3=D.",
        ]),
        ("F. GPIO assignment (approved 2026-10-01)", [
            "D0=GPIO1 XSHUT_L | D1=GPIO2 XSHUT_R | D2=GPIO3 LED_L PWM (strapping pin, gate pulled low) | D3=GPIO4 LED_R PWM",
            "D4=GPIO5 SDA | D5=GPIO6 SCL | D6/D7=GPIO43/44 reserved UART | D8/D9=GPIO7/8 = ToF GPIO1 via DNP links R15/R16 (shared with Sense microSD) | 5V: SJ option only",
            "Firmware: drive both XSHUT low first, release one at a time and change the VL53L1X address (default 0x29 7-bit = 0x52 8-bit).",
        ]),
        ("G. UNVERIFIED / WARNINGS", [
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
